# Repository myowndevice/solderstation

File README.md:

## Цифровая паяльная станция

Паяльная станция - специальный прибор для автоматической регулировки температуры жала обычного паяльника на 220в или для управления паяльным термофеном.
Полностью цифровой вариант.
Для измерения термопары используется самый современный метод - внешний 18-ти битный сигма-дельта ADC. Для управления вентилятором фена - ШИМ модуляция и MOSFET. PID регулятор температуры с возможностью различных настроек для фена и паяльника.

Ключевые особенности самодельной паяльной станции:
- Компактный размер
- Встроенный блок питания на 220В
- Возможность определения вида нагревателя (2 прибора, паяльник и фен)
- Цифровая регулировка мощности нагревателя на основе PID регулятора
- Возможность управления паяльником постоянного напряжения до 24В
- Возможность управления вентилятором термофена (4 скорости)
- Управление нагрузкой целыми полуволнами, с учётом перехода через 0 (меньше помех)
- Защита от перегрева нагревателя
- Индикатор температуры и скорости вентилятора
- Управление тактовыми кнопками
- Защита от ложных срабатываний управляющего симистора с помощью снаббера
- Максимальный ток нагрузки 3 А, что составляет 600 вт без радиатора.

Данный репозитарий содержит все необходимые файлы для сборки цифровой паяльной станции. Если вы будете скачивать файлы через web не забудьте скачать общую папку Kicadlib.

Ознакомится со схемой и подробным описанием данного прибора, программы, и порядка сборки можно, [прочитав эту подробную статью](http://myowndevice.ru/index.php/pribory/item/19-payalnaya-stantsiya)

Также [здесь](http://myowndevice.ru) вы найдете подробное описание как сделать другие приборы, много теории о том, как их делать, методику изготовления печатных плат и много другого.

Изучай микроконтроллеры, разрабатывай и делай электронику дома сам!

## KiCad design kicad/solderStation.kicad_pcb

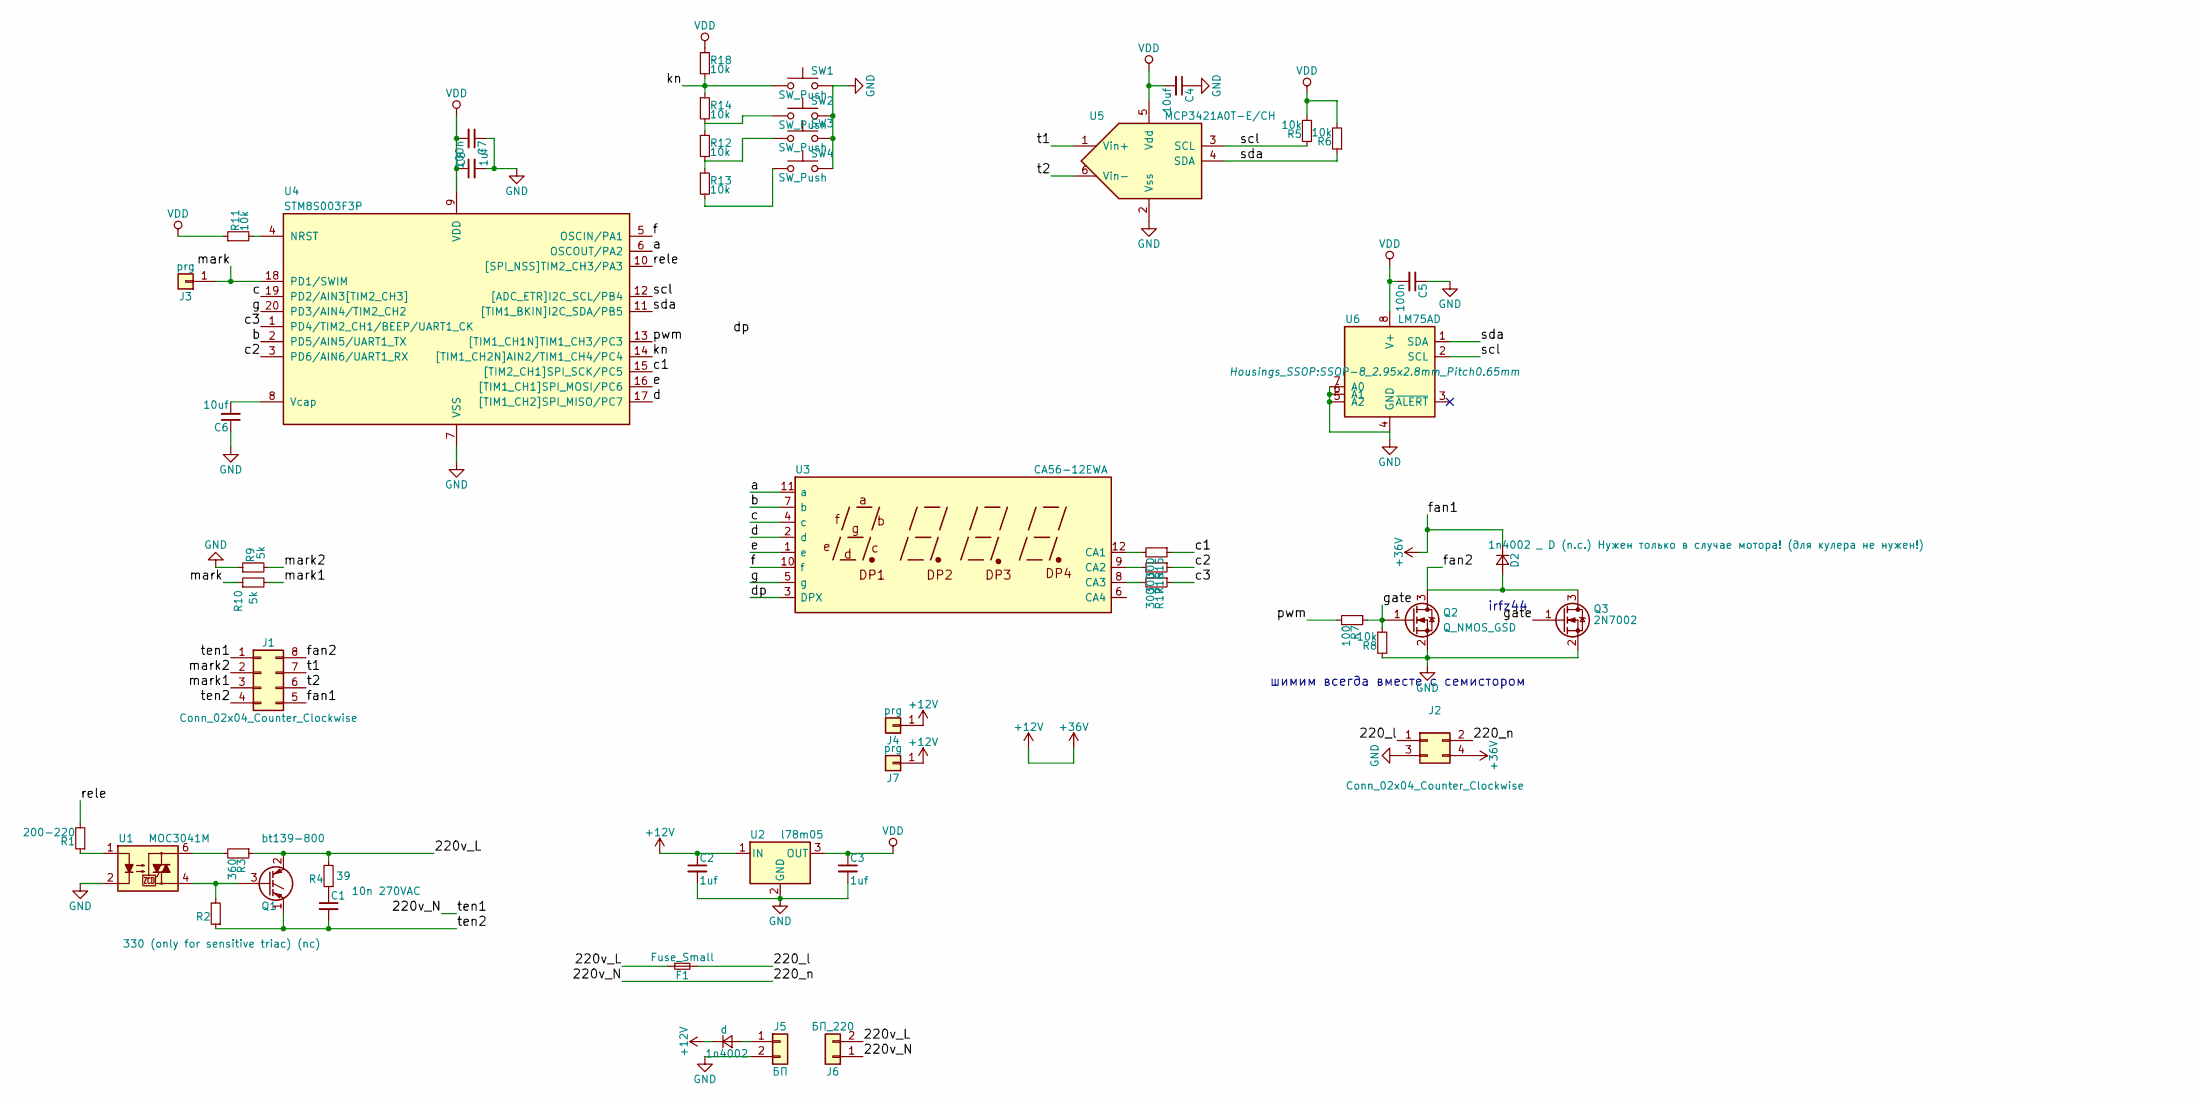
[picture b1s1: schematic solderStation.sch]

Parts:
C1: 10n 270VAC; C_Rect_L13.0mm_W5.0mm_P10.00mm_FKS3_FKP3_MKS4
C2, C3, C8: 1uf; C_0805_HandSoldering
C4, C6: 10uf; C_0805_HandSoldering
C5, C7: 100n; C_0603_HandSoldering
D2: 1n4002 _ D (n.c.) Нужен только в случае мотора! (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; D_MiniMELF
F1: Fuse_Small; Fuseholder5x20_horiz_open_inline_Type-I
J1: Conn_02x04_Counter_Clockwise; Molex_MiniFit-JR-5569-08A2_2x04x4.20mm_Angled
J2: Conn_02x04_Counter_Clockwise; Molex_MiniFit-JR-5569-04A2_2x02x4.20mm_Angled
J3: prg; wirepad_mini
J4, J7: prg; wirepadme
J5: БП; Pin_Header_Straight_1x02_Pitch2.54mm
J6: БП_220; Pin_Header_Straight_1x02_Pitch2.54mm
Q1: bt139-800; TO-220-3_Horizontal_Reversed
Q2: Q_NMOS_GSD; TO-252-2
Q3: 2N7002; SOT-23
R1: 200-220; R_0603_HandSoldering
R2: 330 (only for sensitive triac) (nc); R_Axial_DIN0207_L6.3mm_D2.5mm_P10.16mm_Horizontal
R3: 360; R_Axial_DIN0207_L6.3mm_D2.5mm_P10.16mm_Horizontal
R4: 39; R_Axial_DIN0207_L6.3mm_D2.5mm_P10.16mm_Horizontal
R5, R6, R8, R11, R12, R13, R14, R18: 10k; R_0603_HandSoldering
R7: 100; R_0603_HandSoldering
R9, R10: 5k; R_0603_HandSoldering
R15, R16, R17: 300; R_0603_HandSoldering
SW1, SW2, SW3, SW4: SW_Push; SW_PUSH_6mm
U1: MOC3041M; DIP-6_W7.62mm_LongPads
U2: l78m05; TO-252-2_Rectifier
U3: CA56-12EWA; indicator_3cif
U4: STM8S003F3P; TSSOP-20_4.4x6.5mm_Pitch0.65mm
U5: MCP3421A0T-E/CH; SOT-23-6_Handsoldering
U6: LM75AD; SSOP-8_2.95x2.8mm_Pitch0.65mm
d: 1n4002; D_MiniMELF

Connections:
+12V: C2.1, D2.1 (K), J1.5, J2.4, J4.1, J7.1, U2.1 (IN), d.1 (K); also elsewhere on the board
/220_l: F1.2, J2.1
/220_n: J1.1, J2.2, J6.1
/220v_L: F1.1, J6.2, Q1.2 (C), R3.1, R4.2
/a: U3.11 (a), U4.6 (OSCOUT/PA2)
/b: U3.7 (b), U4.2 (PD5/AIN5/UART1_TX)
/c: U3.4 (c), U4.19 (PD2/AIN3[TIM2_CH3])
/c1: R15.1, U4.15 ([TIM2_CH1]SPI_SCK/PC5)
/c2: R16.1, U4.3 (PD6/AIN6/UART1_RX)
/c3: R17.1, U4.1 (PD4/TIM2_CH1/BEEP/UART1_CK)
/d: U3.2 (d), U4.17 ([TIM1_CH2]SPI_MISO/PC7)
/e: U3.1 (e), U4.16 ([TIM1_CH1]SPI_MOSI/PC6)
/f: U3.10 (f), U4.5 (OSCIN/PA1)
/fan2: D2.2 (A), J1.8, Q2.3 (D), Q3.3 (D)
/g: U3.5 (g), U4.20 (PD3/AIN4/TIM2_CH2)
/gate: Q2.1 (G), Q3.1 (G), R7.1, R8.2
/kn: R14.1, R18.2, SW1.1, U4.14 ([TIM1_CH2N]AIN2/TIM1_CH4/PC4)
/mark: J3.1, R10.1, U4.18 (PD1/SWIM)
/mark1: J1.3, R10.2
/mark2: J1.2, R9.2
/pwm: R7.2, U4.13 ([TIM1_CH1N]TIM1_CH3/PC3)
/rele: R1.2, U4.10 ([SPI_NSS]TIM2_CH3/PA3)
/scl: R5.1, U4.12 ([ADC_ETR]I2C_SCL/PB4), U5.3 (SCL), U6.2 (SCL)
/sda: R6.1, U4.11 ([TIM1_BKIN]I2C_SDA/PB5), U5.4 (SDA), U6.1 (SDA)
/t1: J1.7, U5.1 (Vin+)
/t2: J1.6, U5.6 (Vin-)
/ten2: C1.2, J1.4, Q1.1 (E), R2.1
GND: C2.2, C3.2, C4.1, C5.1, C6.1, C7.1, C8.2, J2.3, J5.2, Q2.2 (S), Q3.2 (S), R8.1, R9.1, SW1.2, SW2.2, SW3.2, SW4.2, U1.2, U2.2 (GND), U4.7 (VSS), U5.2 (Vss), U6.4 (GND), U6.5 (A2), U6.6 (A1), U6.7 (A0)
unnamed: C1.1, R4.1
unnamed: C6.2, U4.8 (Vcap)
unnamed 30: J5.1, d.2 (A); also elsewhere on the board
unnamed: Q1.3 (G), R2.2, U1.4
unnamed: R1.1, U1.1
unnamed: R3.2, U1.6
unnamed: R11.2, U4.4 (NRST)
unnamed: R12.1, R14.2, SW2.1
unnamed: R12.2, R13.1, SW3.1
unnamed: R13.2, SW4.1
unnamed: R15.2, U3.12 (CA1)
unnamed: R16.2, U3.9 (CA2)
unnamed: R17.2, U3.8 (CA3)
VDD: C3.1, C4.2, C5.2, C7.2, C8.1, R5.2, R6.2, R11.1, R18.1, U2.3 (OUT), U4.9 (VDD), U5.5 (Vdd), U6.8 (V+)

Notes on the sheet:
irfz44
шимим всегда вместе с семистором

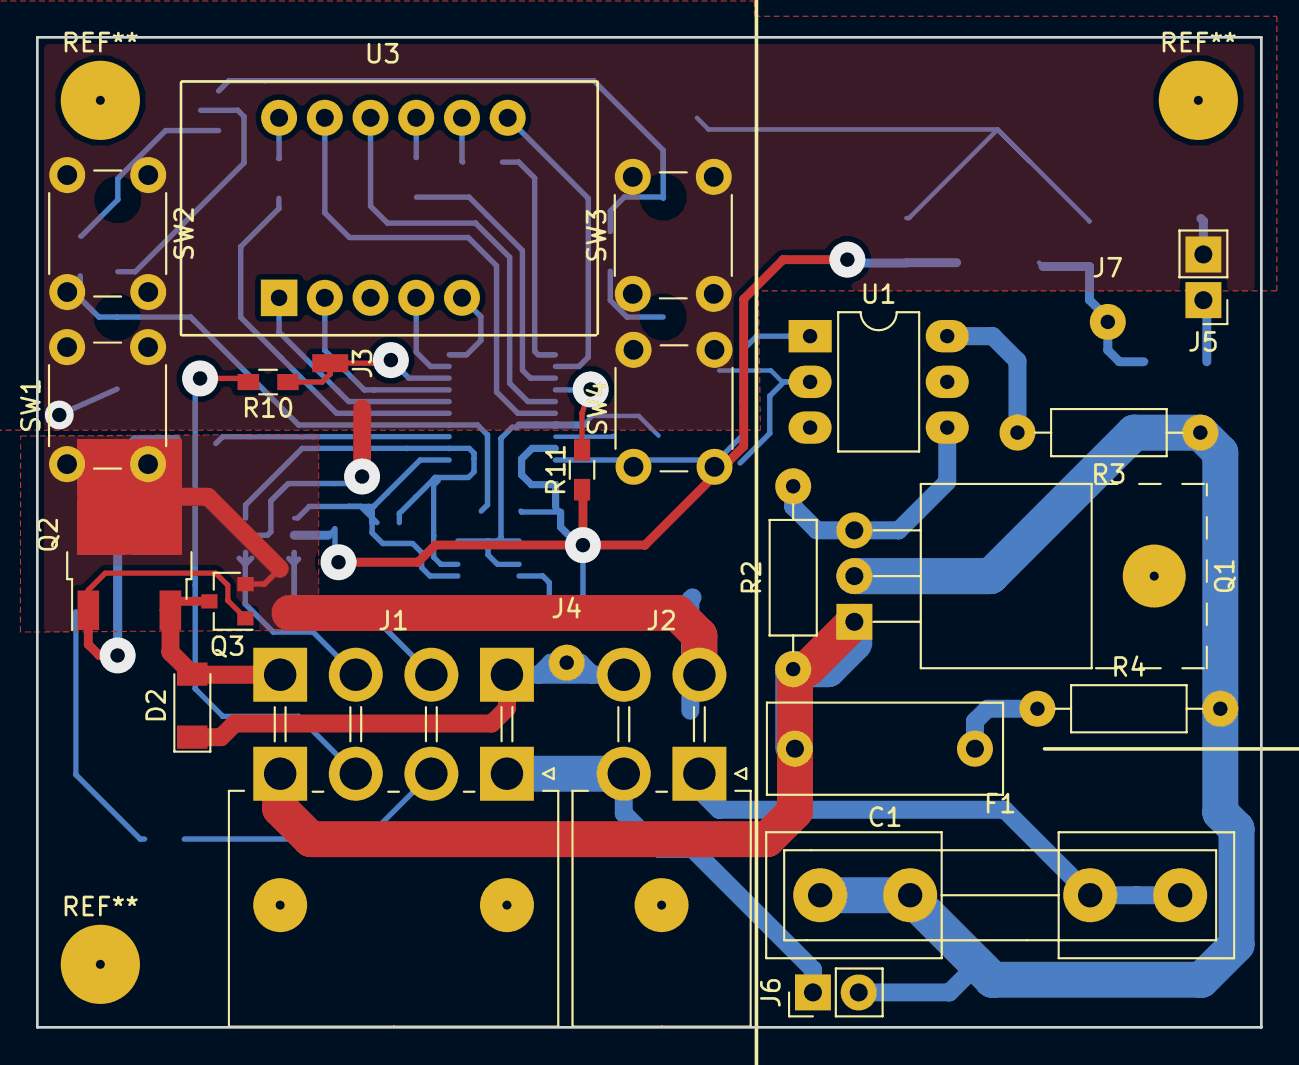
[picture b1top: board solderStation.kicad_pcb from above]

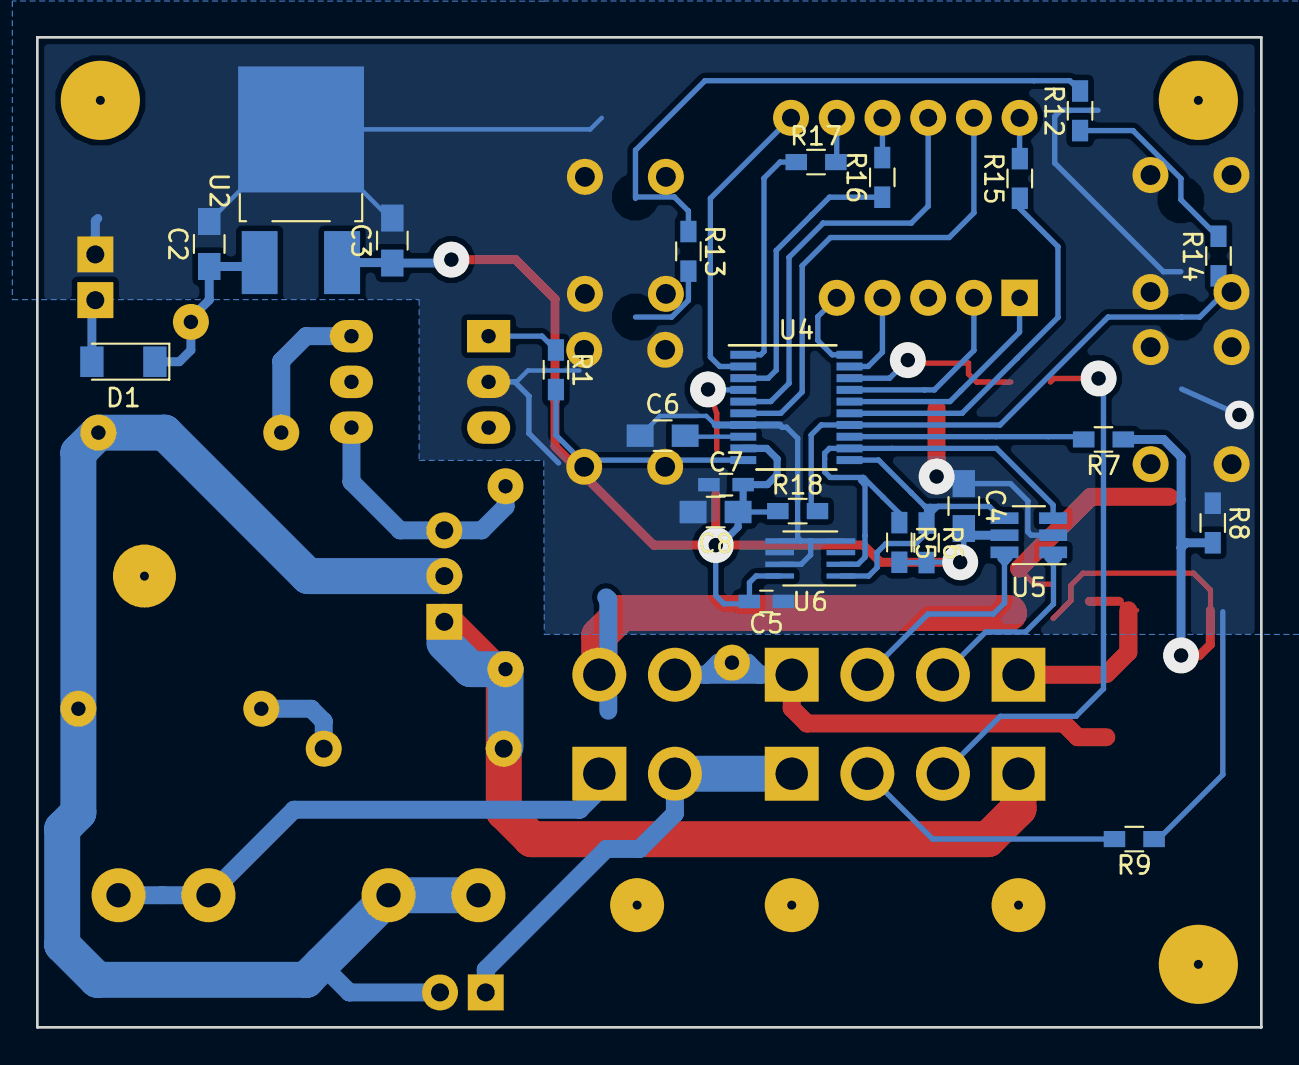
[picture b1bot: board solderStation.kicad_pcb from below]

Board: 2 copper layers, 68.0 x 55.0 mm, 49 parts (25 on the bottom side), 42 nets.

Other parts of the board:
D1: D_Small; D_MiniMELF

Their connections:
+12V: D1.1; also elsewhere on the board
unnamed 30: D1.2; also elsewhere on the board

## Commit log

2020-04-30 start
